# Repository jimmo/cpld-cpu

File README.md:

## CPLD CPU

This is a project to create a demonstration CPU that is simple enough to be able to watch its execution but also able to do something almost useful.

It was inspired by the following five projects:
 - [Fourbit, by Jaromir Sukuba](http://jaromir.xf.cz/fourbit/fourbit.html). This is a 4-bit CPU made entirely from 74xx series logic.
 - [Tiny CPU in a CPLD, by Big Mess o' Wires](https://www.bigmessowires.com/cpu-in-a-cpld/). This implements a whole CPU inside a single Altera CPLD.
 - [MCPU, by Tim Böscke](https://github.com/cpldcpu/MCPU) (and [writeup, by Jean-Claude Wippler](https://jeelabs.org/2017/11/tfoc---a-minimal-computer/)). Similar to above, but using the exact CPLD that I was intending to use, and with a really well-documented and practical ISA.
 - [The Megaprocessor, by James Newman](http://megaprocessor.com/). "The Megaprocessor is a micro-processor built large. Very large." Each gate is made from through-hole transistors with LEDs on all inputs and outputs.
 - [monster6502, by TubeTime & Evil Mad Scientist Laboratories](https://monster6502.com/). A working replica of the 6502 using discrete SMT transistors, complete with loads of LEDs.

In particular the CPU design (ISA and architecture) is inspired by Fourbit, Tiny CPU, and especially MPU, while the exploded design and "LEDs everywhere" is inspired by the Megaprocessor and monster6502. While nowhere near as capable as monster6502 or the Megaprocessor, it is definitely much more budget-friendly! And it can still [compute prime numbers](pysim/cpu_ax_13/tests/primes.s) ([video](https://www.youtube.com/watch?v=ZP9e-FCwwOs)) and [drive APA102 LED strips](pysim/cpu_ax_13/tests/apa102c.s).

Also, while not a direct inspiration to this project, it's absolutely worth linking to [Breadboard 8-bit computer, by Ben Eater](https://eater.net/8bit) which is a wonderful series about a similar project.

## History

This idea started when I was teaching an introduction to "how CPUs work", and wanted something tangible to show my students. The goal is to show how simple logic circuits (i.e. starting with AND and OR gates, flip flops, and a clock) can work together to do computation. No magic required.

Initially I planned to exactly replicate the Fourbit (possibly upgraded to 8-bit), but had trouble sourcing the 74181 ALU. I found a [XC9572XL CPLD development board](http://dangerousprototypes.com/blog/2011/03/29/new-prototype-xc9572xl-cpld-development-board/) in my board collection and considered replicating the 74181 on that. CPLDs are really useful for a project like this because they do not require external flash for configuration. You can use them almost as a complete drop-in replacement. However, at this point if you're not constraining yourself to using exactly 74xx series parts, then there are several simplifications you can make in the Fourbit design.

So I set about designing a CPU where each functional component is its own CPLD. In some ways this is similar to designing a soft-CPU for an FPGA, but with the additional constraint that signals between components actually need to go via physical pins. For an 8-bit CPU, this uses up a lot of pins very quickly.

For a fun side-quest, I wrote a [logic simulator](pysim) that allows a logic circuit to be defined in Python, and simulated, much the same way that [Verilator](https://www.veripool.org/verilator/) can simulate an HDL file. This allowed me to test and iterate on some different designs, including an [exact clone of the MCPU design](pysim/cpu_a_6). Additionally the simulator allows me to stay closer to my original goal of being able to describe every logic gate, although some shortcuts were taken.

The [final design](pysim/cpu_ax_13) expands on the MCPU design, including 13-bit addressing, an index register, two-byte instruction encoding, a primitive MMU allowing addressing up to 1MiB of physical RAM, and memory-mapped IO. The memory is von Neumann, allowing for RAM and ROM to share the same bus. The simulator allowed some [programs to be written](pysim/cpu_ax_13/tests) and tested, including an assembler supporting some macro commands.

Once that was working, I translated each Python component into VHDL, and tested it on the CPLD breakout board. For example, here's the decoder ([Python](pysim/cpu_ax_13/cpu.py#L51) and [VHDL](gateware/decoder/decoder.vhd)). The most difficult part of this process, and possibly the whole project, was [uploading the gateware to the CPLD](https://blog.jimmo.id.au/2018/11/26/programming-a-xc9500xl-cpld-with-a-raspberry-pi.html). In order to keep the design simple, the clock is generated by a ring oscillator in the clock CPLD, which is a terrible idea in general but works well here.

Finally, I designed [a schematic](hardware/schematic.pdf) and [PCB layout](hardware), which mostly involved laying out 131 LEDs (and their current limiting resistors). Rather than putting both RAM and ROM into the design, it just has a single RAM chip. This means that it has no persistent program storage, and the program needs to be loaded by an external programmer (implemented using some spare pins on the memory controller).

It's a four-layer PCB and can be assembled by hand with an iron or hot air. The CPLDs are TQFP and the LEDs and resistors are all 0805.

Other than occasionally being used for teaching, I mostly keep it mounted on the wall with the clock speed set to \~5Hz, forever [computing prime numbers](pysim/cpu_ax_13/tests/primes.s). It's quite mesmerizing to [watch](https://www.youtube.com/watch?v=ZP9e-FCwwOs)!

## Features

 - All internal state visible via 131 LEDs. This includes:
   - A, X, PC, Instr, and Addr registers (including carry & zero flags).
   - Data bus (and output/input state of each connected component)
   - Memory address
   - Clock
   - Decoder state
   - GPIO
 - 8-bit accumulator
 - 8-bit index register
 - 16-bit program counter
 - 8 instructions (nor a, add a, sta, jcc, nor x, add x, stx, jnz)
 - Variable-speed clock (Hz to >100kHz), including single-instruction and single-cycle step.
 - Expansion header (allowing for memory-mapped peripherals)
 - 8-bit memory-mapped GPIO port (input and output, with jumpered LEDs on each)
 - Serial programming header

## Instruction set

The instruction set is heavily inspired by MCPU. See their [project description](https://github.com/cpldcpu/MCPU/blob/master/mcpu.pdf?raw=true) and [blog post](https://jeelabs.org/2017/11/tfoc---a-minimal-computer/) for more information. The main extension is the addition of the index register (X) as well as a jump-non-zero.

### Hardware instructions

#### nor [mem]
`A = A nor [mem + X]`

#### add
`A = A + [mem + X]`

#### sta
`[mem + X] = A`

#### jcc
Jump if carry not set.

#### norx
`X = X nor [X]`

#### addx
`X = X + [mem]`

#### stx
`[mem] = X`

#### jnz
Jump if zero flag not set.

#### Pseudo instructions

These are supported by the assembler and generate a sequence of real instructions.

#### clr
`A = 0`

#### lda
`A = [mem]`

#### not
`A = ~A`

#### sub
`A = A - [mem + X]`

#### clrx
`X = 0`

#### ldx
`X = [mem]`

#### notx
`X = ~X`

#### subx
`X = X - [mem]`

#### jmp
Unconditional jump

#### jcs
Jump if carry flag set

#### jz
Jump if zero flag set

#### shl
`A = A << 1`

#### inc
`A = A + 1`

#### dec
`A = A - 1`

#### and
`A = A & [mem + X]`

#### or
`A = A | [mem + X]`

#### nand
`A = ~(A & [mem + X])`

#### xnor
`A = ~(A ^ [mem + X])`

#### xor
`A = A ^ [mem + X]`

#### ldpg
Sets the current memory page

#### hlt
Infinite loop

#### out
(Simulator only) prints A to stdout

## Programming

There's a [MicroPython script](programmer) that can load a assembled binary via the serial programming interface (header is next to the memory controller).

## TODO

 - Much more documentation and assembly guide (I'd love to do a video series one day)
 - Better demos
 - A higher-level compiler, making better use of the MMU
 - Design a peripheral to use the expansion connector
 - Use an external clock (and find out how fast this can go).

## Ideas for future revisions

 - Separate net for the LED ground (allowing it to be disconnected).
 - Fix the missing PC_LOW LED (bodged in on the current board)
 - More LEDs (e.g. ALU current operation)

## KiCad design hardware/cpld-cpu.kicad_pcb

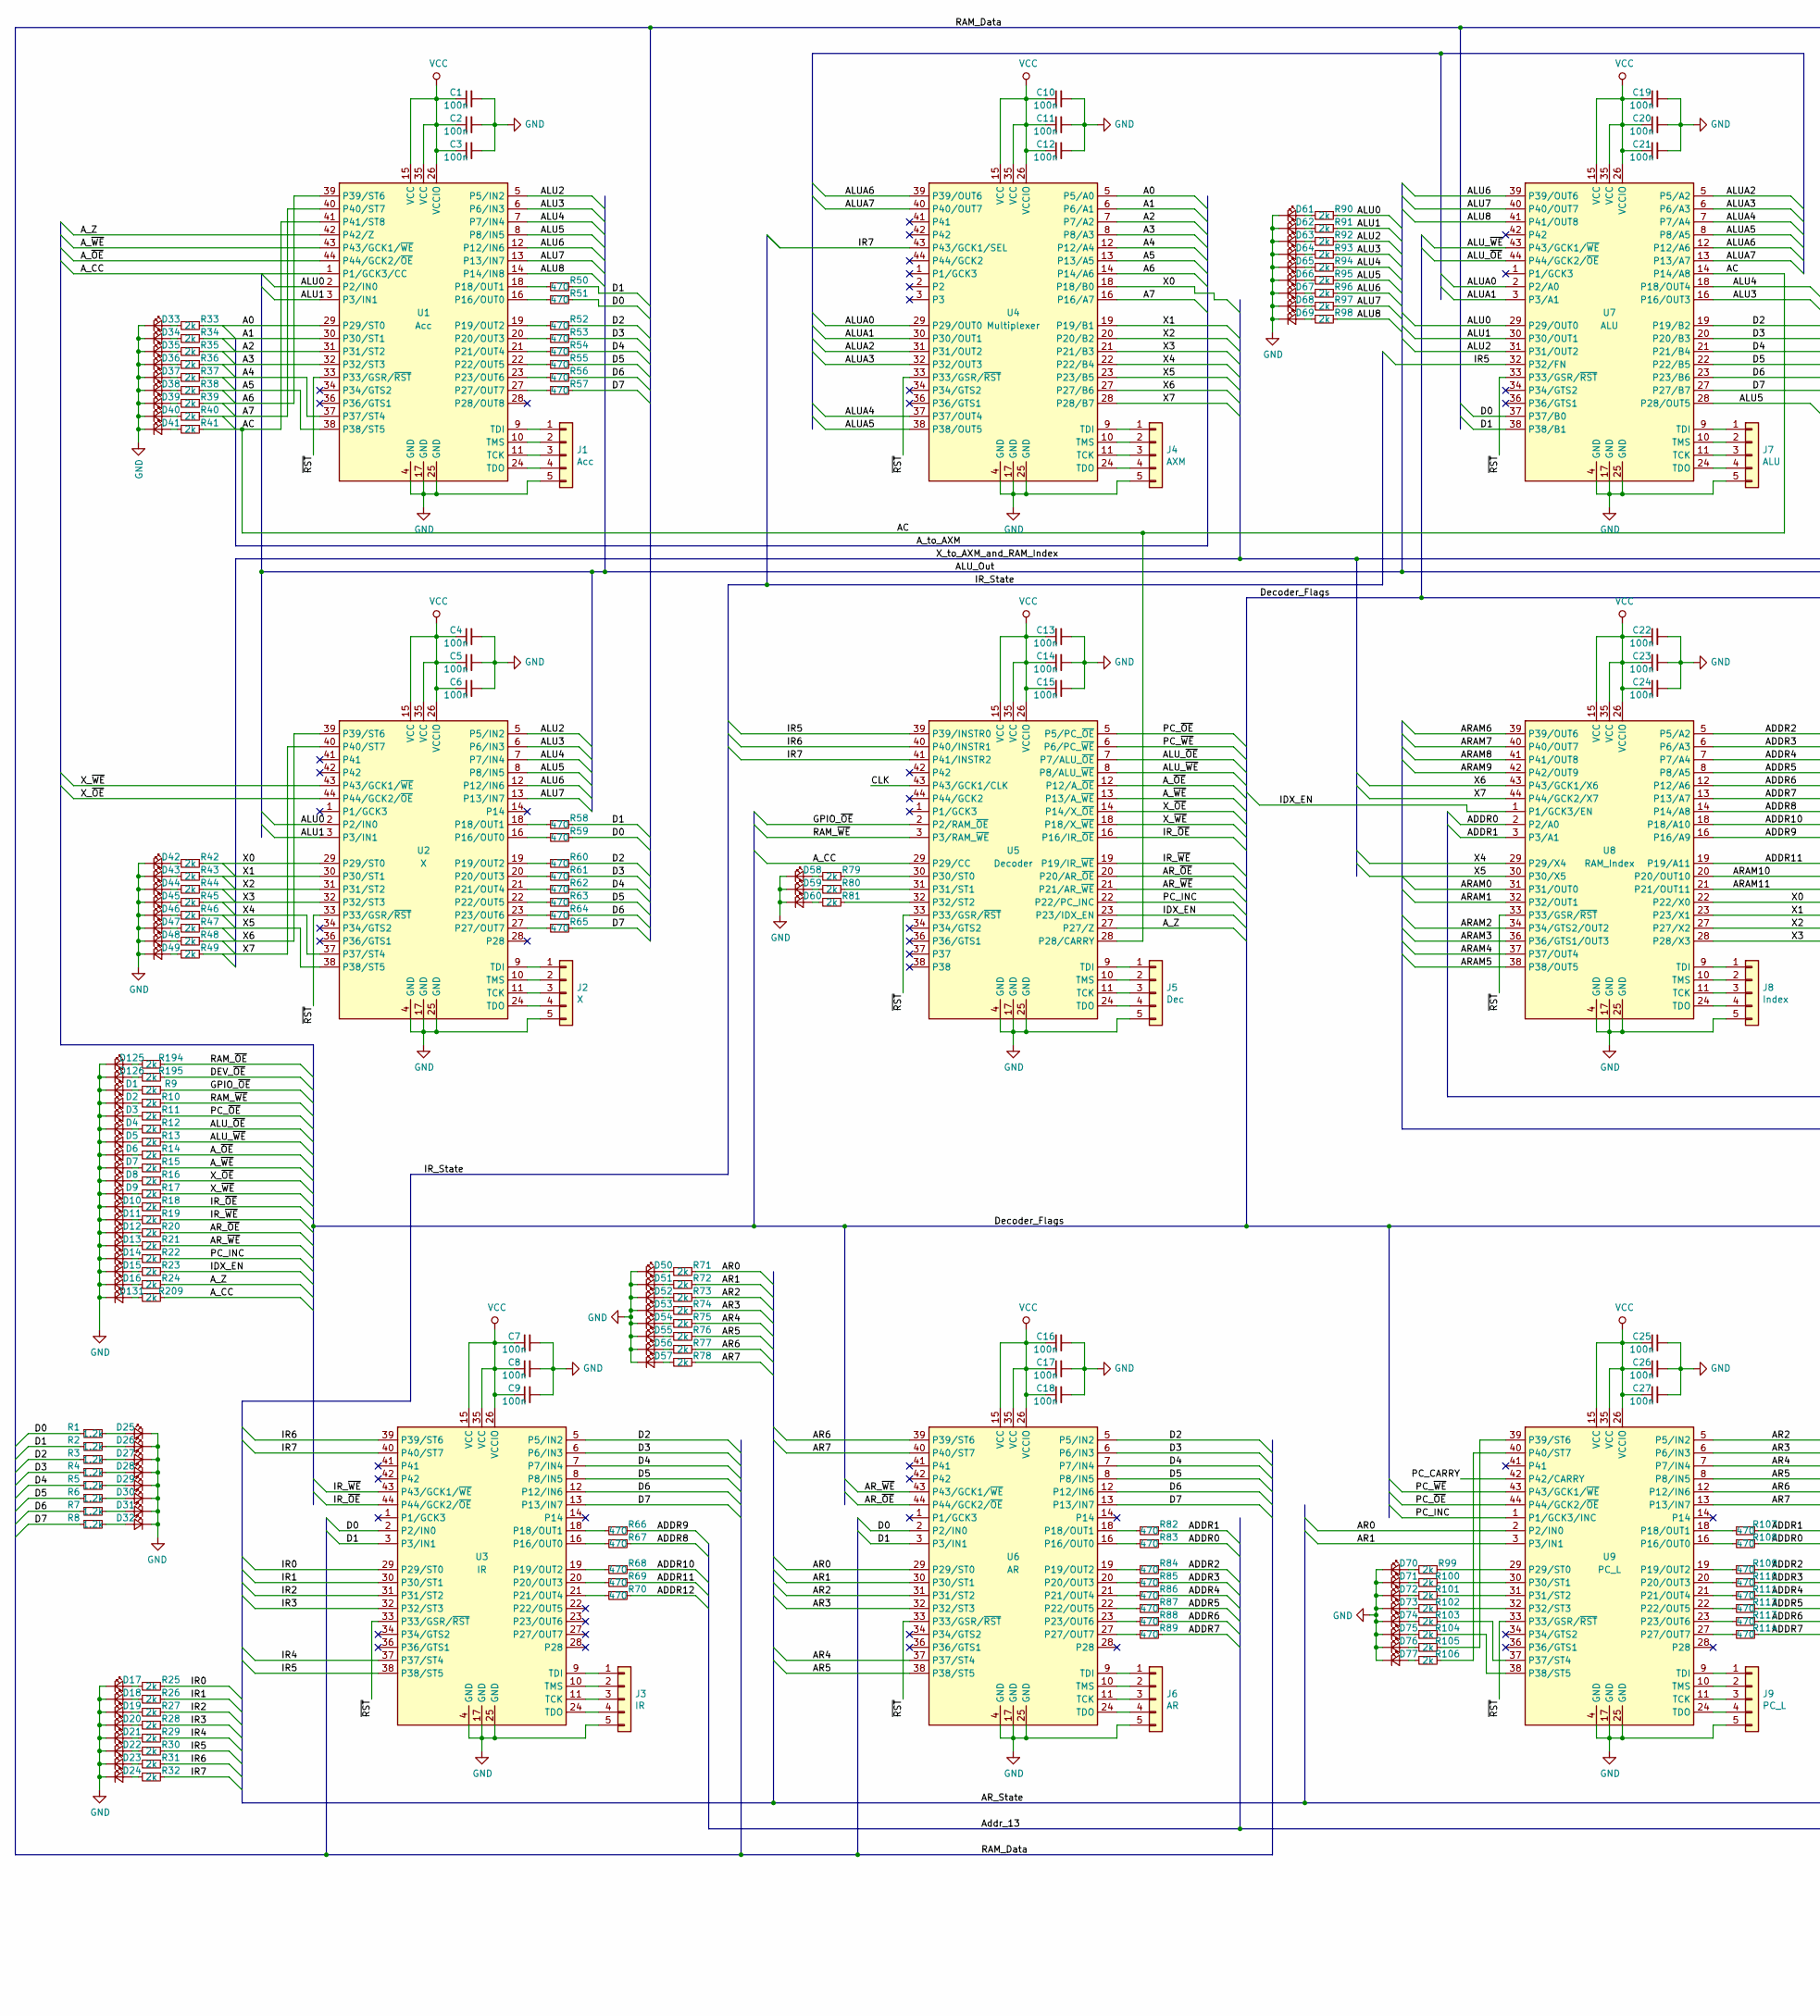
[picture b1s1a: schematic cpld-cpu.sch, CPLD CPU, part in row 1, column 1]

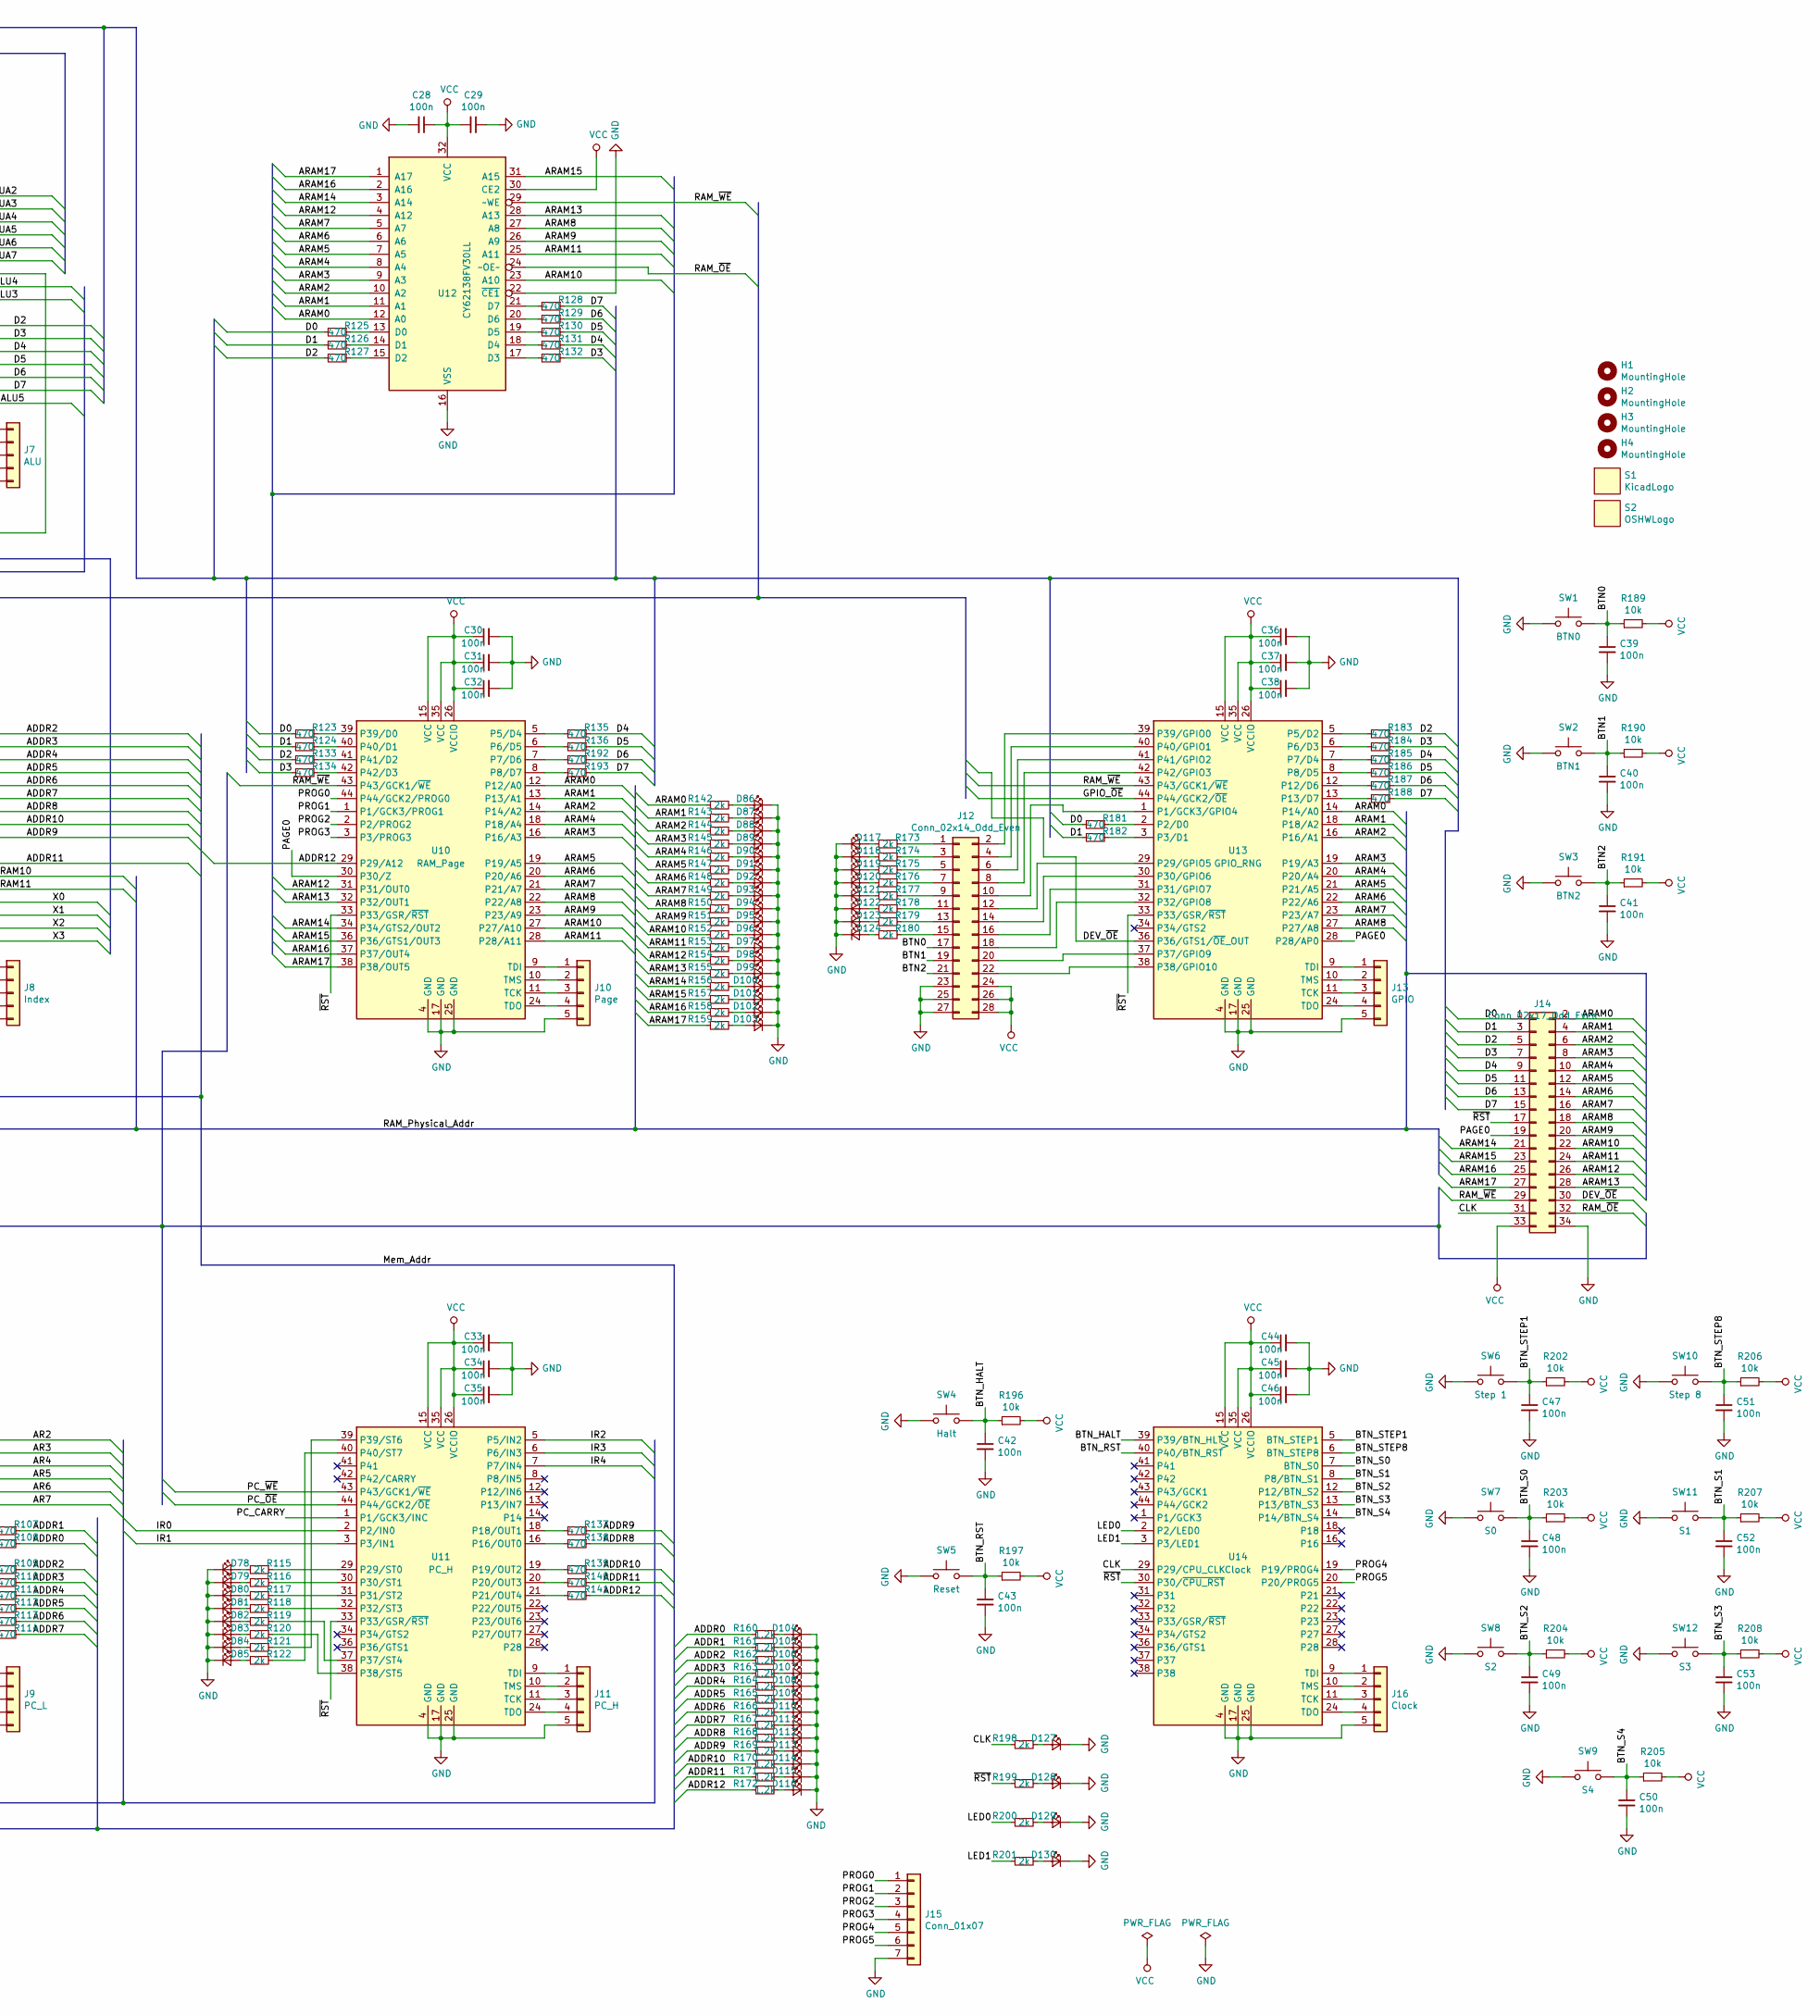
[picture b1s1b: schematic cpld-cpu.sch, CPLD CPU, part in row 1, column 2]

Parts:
C1, C2, C3, C4, C5, C6, C7, C8, C9, C10, C11, C12, C13, C14, C15, C16, C17, C18, C19, C20, C21, C22, C23, C24, C25, C26, C27, C28, C29, C30, C31, C32, C33, C34, C35, C36, C37, C38, C39, C40, C41, C42, C43, C44, C45, C46, C47, C48, C49, C50, C51, C52, C53: 100n; C_0805_HandSoldering
D1, D2, D3, D4, D5, D6, D7, D8, D9, D10, D11, D12, D13, D14, D15, D16, D17, D18, D19, D20, D21, D22, D23, D24, D25, D26, D27, D28, D29, D30, D31, D32, D33, D34, D35, D36, D37, D38, D39, D40, D41, D42, D43, D44, D45, D46, D47, D48, D49, D50, D51, D52, D53, D54, D55, D56, D57, D58, D59, D60, D61, D62, D63, D64, D65, D66, D67, D68, D69, D70, D71, D72, D73, D74, D75, D76, D77, D78, D79, D80, D81, D82, D83, D84, D85, D86, D87, D88, D89, D90, D91, D92, D93, D94, D95, D96, D97, D98, D99, D100, D101, D102, D103, D104, D105, D106, D107, D108, D109, D110, D111, D112, D113, D114, D115, D116, D117, D118, D119, D120, D121, D122, D123, D124, D125, D126, D127, D128, D129, D130, D131: LED_Small; LED_0805_HandSoldering
H1, H2, H3, H4: MountingHole; MountingHole_4.3mm_M4
J1: Acc; Pin_Header_Straight_1x05_Pitch2.54mm
J2: X; Pin_Header_Straight_1x05_Pitch2.54mm
J3: IR; Pin_Header_Straight_1x05_Pitch2.54mm
J4: AXM; Pin_Header_Straight_1x05_Pitch2.54mm
J5: Dec; Pin_Header_Straight_1x05_Pitch2.54mm
J6: AR; Pin_Header_Straight_1x05_Pitch2.54mm
J7: ALU; Pin_Header_Straight_1x05_Pitch2.54mm
J8: Index; Pin_Header_Straight_1x05_Pitch2.54mm
J9: PC_L; Pin_Header_Straight_1x05_Pitch2.54mm
J10: Page; Pin_Header_Straight_1x05_Pitch2.54mm
J11: PC_H; Pin_Header_Straight_1x05_Pitch2.54mm
J12: Conn_02x14_Odd_Even; Pin_Header_Straight_2x14_Pitch2.54mm
J13: GPIO; Pin_Header_Straight_1x05_Pitch2.54mm
J14: Conn_02x17_Odd_Even; Pin_Header_Straight_2x17_Pitch2.54mm
J15: Conn_01x07; Pin_Header_Straight_1x07_Pitch2.54mm
J16: Clock; Pin_Header_Straight_1x05_Pitch2.54mm
R1, R2, R3, R4, R5, R6, R7, R8, R160, R161, R162, R163, R164, R165, R166, R167, R168, R169, R170, R171, R172: 1.2k; R_0805_HandSoldering
R9, R10, R11, R12, R13, R14, R15, R16, R17, R18, R19, R20, R21, R22, R23, R24, R25, R26, R27, R28, R29, R30, R31, R32, R33, R34, R35, R36, R37, R38, R39, R40, R41, R42, R43, R44, R45, R46, R47, R48, R49, R71, R72, R73, R74, R75, R76, R77, R78, R79, R80, R81, R90, R91, R92, R93, R94, R95, R96, R97, R98, R99, R100, R101, R102, R103, R104, R105, R106, R115, R116, R117, R118, R119, R120, R121, R122, R142, R143, R144, R145, R146, R147, R148, R149, R150, R151, R152, R153, R154, R155, R156, R157, R158, R159, R173, R174, R175, R176, R177, R178, R179, R180, R194, R195, R198, R199, R200, R201, R209: 2k; R_0805_HandSoldering
R50, R51, R52, R53, R54, R55, R56, R57, R58, R59, R60, R61, R62, R63, R64, R65, R66, R67, R68, R69, R70, R82, R83, R84, R85, R86, R87, R88, R89, R107, R108, R109, R110, R111, R112, R113, R114, R123, R124, R125, R126, R127, R128, R129, R130, R131, R132, R133, R134, R135, R136, R137, R138, R139, R140, R141, R181, R182, R183, R184, R185, R186, R187, R188, R192, R193: 470; R_0805_HandSoldering
R189, R190, R191, R196, R197, R202, R203, R204, R205, R206, R207, R208: 10k; R_0805_HandSoldering
S1: KicadLogo; Symbol_KiCAD-Logo_CopperAndSilkScreenTop
S2: OSHWLogo; OSHW-Logo2_14.6x12mm_Copper_Top
SW1: BTN0; SW_SPST_B3S-1000
SW2: BTN1; SW_SPST_B3S-1000
SW3: BTN2; SW_SPST_B3S-1000
SW4: Halt; SW_SPST_B3S-1000
SW5: Reset; SW_SPST_B3S-1000
SW6: Step 1; SW_SPST_B3S-1000
SW7: S0; SW_SPST_B3S-1000
SW8: S2; SW_SPST_B3S-1000
SW9: S4; SW_SPST_B3S-1000
SW10: Step 8; SW_SPST_B3S-1000
SW11: S1; SW_SPST_B3S-1000
SW12: S3; SW_SPST_B3S-1000
U1: Acc; TQFP-44_10x10mm_Pitch0.8mm
U2: X; TQFP-44_10x10mm_Pitch0.8mm
U3: IR; TQFP-44_10x10mm_Pitch0.8mm
U4: Multiplexer; TQFP-44_10x10mm_Pitch0.8mm
U5: Decoder; TQFP-44_10x10mm_Pitch0.8mm
U6: AR; TQFP-44_10x10mm_Pitch0.8mm
U7: ALU; TQFP-44_10x10mm_Pitch0.8mm
U8: RAM_Index; TQFP-44_10x10mm_Pitch0.8mm
U9: PC_L; TQFP-44_10x10mm_Pitch0.8mm
U10: RAM_Page; TQFP-44_10x10mm_Pitch0.8mm
U11: PC_H; TQFP-44_10x10mm_Pitch0.8mm
U12: CY62138FV30LL; TSOP-II-32_21.0x10.2mm_Pitch1.27mm
U13: GPIO_RNG; TQFP-44_10x10mm_Pitch0.8mm
U14: Clock; TQFP-44_10x10mm_Pitch0.8mm

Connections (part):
/A0: R33.1, U1.29 (P29/ST0), U4.5 (P5/A0)
/A1: R34.1, U1.30 (P30/ST1), U4.6 (P6/A1)
/A2: R35.1, U1.31 (P31/ST2), U4.7 (P7/A2)
/A3: R36.1, U1.32 (P32/ST3), U4.8 (P8/A3)
/A4: R37.1, U1.37 (P37/ST4), U4.12 (P12/A4)
/A5: R38.1, U1.38 (P38/ST5), U4.13 (P13/A5)
/A6: R39.1, U1.39 (P39/ST6), U4.14 (P14/A6)
/A7: R40.1, U1.40 (P40/ST7), U4.16 (P16/A7)
/AC: R41.1, U1.41 (P41/ST8), U5.28 (P28/CARRY), U7.14 (P14/A8)
/ADDR0: R83.1, R108.1, R160.1, U8.2 (P2/A0)
/ADDR1: R82.1, R107.1, R161.1, U8.3 (P3/A1)
/ADDR2: R84.1, R109.1, R162.1, U8.5 (P5/A2)
/ADDR3: R85.1, R110.1, R163.1, U8.6 (P6/A3)
/ADDR4: R86.1, R111.1, R164.1, U8.7 (P7/A4)
/ADDR5: R87.1, R112.1, R165.1, U8.8 (P8/A5)
/ADDR6: R88.1, R113.1, R166.1, U8.12 (P12/A6)
/ADDR7: R89.1, R114.1, R167.1, U8.13 (P13/A7)
/ADDR8: R67.1, R138.1, R168.1, U8.14 (P14/A8)
/ADDR9: R66.1, R137.1, R169.1, U8.16 (P16/A9)
/ADDR10: R68.1, R139.1, R170.1, U8.18 (P18/A10)
/ADDR11: R69.1, R140.1, R171.1, U8.19 (P19/A11)
/ADDR12: R70.1, R141.1, R172.1, U10.29 (P29/A12)
/ALU0: R90.1, U1.2 (P2/IN0), U2.2 (P2/IN0), U7.29 (P29/OUT0)
/ALU1: R91.1, U1.3 (P3/IN1), U2.3 (P3/IN1), U7.30 (P30/OUT1)
/ALU2: R92.1, U1.5 (P5/IN2), U2.5 (P5/IN2), U7.31 (P31/OUT2)
/ALU3: R93.1, U1.6 (P6/IN3), U2.6 (P6/IN3), U7.16 (P16/OUT3)
/ALU4: R94.1, U1.7 (P7/IN4), U2.7 (P7/IN4), U7.18 (P18/OUT4)
/ALU5: R95.1, U1.8 (P8/IN5), U2.8 (P8/IN5), U7.28 (P28/OUT5)
/ALU6: R96.1, U1.12 (P12/IN6), U2.12 (P12/IN6), U7.39 (P39/OUT6)
/ALU7: R97.1, U1.13 (P13/IN7), U2.13 (P13/IN7), U7.40 (P40/OUT7)
/ALU8: R98.1, U1.14 (P14/IN8), U7.41 (P41/OUT8)
/ALUA0: U4.29 (P29/OUT0), U7.2 (P2/A0)
/ALUA1: U4.30 (P30/OUT1), U7.3 (P3/A1)
/ALUA2: U4.31 (P31/OUT2), U7.5 (P5/A2)
/ALUA3: U4.32 (P32/OUT3), U7.6 (P6/A3)
/ALUA4: U4.37 (P37/OUT4), U7.7 (P7/A4)
/ALUA5: U4.38 (P38/OUT5), U7.8 (P8/A5)
/ALUA6: U4.39 (P39/OUT6), U7.12 (P12/A6)
/ALUA7: U4.40 (P40/OUT7), U7.13 (P13/A7)
/ALU_~OE~: R12.1, U5.7 (P7/ALU_~OE~), U7.44 (P44/GCK2/~OE~)
/ALU_~WE~: R13.1, U5.8 (P8/ALU_~WE~), U7.43 (P43/GCK1/~WE~)
/AR0: R71.1, U6.29 (P29/ST0), U9.2 (P2/IN0)
/AR1: R72.1, U6.30 (P30/ST1), U9.3 (P3/IN1)
/AR2: R73.1, U6.31 (P31/ST2), U9.5 (P5/IN2)
/AR3: R74.1, U6.32 (P32/ST3), U9.6 (P6/IN3)
/AR4: R75.1, U6.37 (P37/ST4), U9.7 (P7/IN4)
/AR5: R76.1, U6.38 (P38/ST5), U9.8 (P8/IN5)
/AR6: R77.1, U6.39 (P39/ST6), U9.12 (P12/IN6)
/AR7: R78.1, U6.40 (P40/ST7), U9.13 (P13/IN7)
/ARAM0: J14.2, R142.1, U8.31 (P31/OUT0), U10.12 (P12/A0), U12.12 (A0), U13.14 (P14/A0)
/ARAM1: J14.4, R143.1, U8.32 (P32/OUT1), U10.13 (P13/A1), U12.11 (A1), U13.18 (P18/A2)
/ARAM2: J14.6, R144.1, U8.34 (P34/GTS2/OUT2), U10.14 (P14/A2), U12.10 (A2), U13.16 (P16/A1)
/ARAM3: J14.8, R145.1, U8.36 (P36/GTS1/OUT3), U10.16 (P16/A3), U12.9 (A3), U13.19 (P19/A3)
/ARAM4: J14.10, R146.1, U8.37 (P37/OUT4), U10.18 (P18/A4), U12.8 (A4), U13.20 (P20/A4)
/ARAM5: J14.12, R147.1, U8.38 (P38/OUT5), U10.19 (P19/A5), U12.7 (A5), U13.21 (P21/A5)
/ARAM6: J14.14, R148.1, U8.39 (P39/OUT6), U10.20 (P20/A6), U12.6 (A6), U13.22 (P22/A6)
/ARAM7: J14.16, R149.1, U8.40 (P40/OUT7), U10.21 (P21/A7), U12.5 (A7), U13.23 (P23/A7)
/ARAM8: J14.18, R150.1, U8.41 (P41/OUT8), U10.22 (P22/A8), U12.27 (A8), U13.27 (P27/A8)
/ARAM9: J14.20, R151.1, U8.42 (P42/OUT9), U10.23 (P23/A9), U12.26 (A9)
/ARAM10: J14.22, R152.1, U8.20 (P20/OUT10), U10.27 (P27/A10), U12.23 (A10)
/ARAM11: J14.24, R153.1, U8.21 (P21/OUT11), U10.28 (P28/A11), U12.25 (A11)
/ARAM12: J14.26, R154.1, U10.31 (P31/OUT0), U12.4 (A12)
/ARAM13: J14.28, R155.1, U10.32 (P32/OUT1), U12.28 (A13)
/ARAM14: J14.21, R156.1, U10.34 (P34/GTS2/OUT2), U12.3 (A14)
/ARAM15: J14.23, R157.1, U10.36 (P36/GTS1/OUT3), U12.31 (A15)
/ARAM16: J14.25, R158.1, U10.37 (P37/OUT4), U12.2 (A16)
/ARAM17: J14.27, R159.1, U10.38 (P38/OUT5), U12.1 (A17)
/AR_~OE~: R20.1, U5.20 (P20/AR_~OE~), U6.44 (P44/GCK2/~OE~)
/AR_~WE~: R21.1, U5.21 (P21/AR_~WE~), U6.43 (P43/GCK1/~WE~)
/A_CC: R209.1, U1.1 (P1/GCK3/CC), U5.29 (P29/CC)
/A_Z: R24.1, U1.42 (P42/Z), U5.27 (P27/Z)
/A_~OE~: R14.1, U1.44 (P44/GCK2/~OE~), U5.12 (P12/A_~OE~)
/A_~WE~: R15.1, U1.43 (P43/GCK1/~WE~), U5.13 (P13/A_~WE~)
/BTN0: C39.1, J12.17, R189.1, SW1.2
/BTN1: C40.1, J12.19, R190.1, SW2.2
/BTN2: C41.1, J12.21, R191.1, SW3.2
/BTN_HALT: C42.1, R196.1, SW4.2, U14.39 (P39/BTN_HLT)
/BTN_RST: C43.1, R197.1, SW5.2, U14.40 (P40/BTN_RST)
/BTN_S0: C48.1, R203.1, SW7.2, U14.7 (BTN_S0)
/BTN_S1: C52.1, R207.1, SW11.2, U14.8 (P8/BTN_S1)
/BTN_S2: C49.1, R204.1, SW8.2, U14.12 (P12/BTN_S2)
/BTN_S3: C53.1, R208.1, SW12.2, U14.13 (P13/BTN_S3)
/BTN_S4: C50.1, R205.1, SW9.2, U14.14 (P14/BTN_S4)
/BTN_STEP1: C47.1, R202.1, SW6.2, U14.5 (BTN_STEP1)
/BTN_STEP8: C51.1, R206.1, SW10.2, U14.6 (BTN_STEP8)
/CLK: J14.31, R198.1, U5.43 (P43/GCK1/CLK), U14.29 (P29/CPU_CLK)
/D0: J14.1, R1.1, R51.1, R59.1, R123.2, R125.2, R181.2, U3.2 (P2/IN0), U6.2 (P2/IN0), U7.37 (P37/B0)
/D1: J14.3, R2.1, R50.1, R58.1, R124.2, R126.2, R182.2, U3.3 (P3/IN1), U6.3 (P3/IN1), U7.38 (P38/B1)
/D2: J14.5, R3.1, R52.1, R60.1, R127.2, R133.2, R183.1, U3.5 (P5/IN2), U6.5 (P5/IN2), U7.19 (P19/B2)
/D3: J14.7, R4.1, R53.1, R61.1, R132.1, R134.2, R184.1, U3.6 (P6/IN3), U6.6 (P6/IN3), U7.20 (P20/B3)
/D4: J14.9, R5.1, R54.1, R62.1, R131.1, R135.1, R185.1, U3.7 (P7/IN4), U6.7 (P7/IN4), U7.21 (P21/B4)
/D5: J14.11, R6.1, R55.1, R63.1, R130.1, R136.1, R186.1, U3.8 (P8/IN5), U6.8 (P8/IN5), U7.22 (P22/B5)
/D6: J14.13, R7.1, R56.1, R64.1, R129.1, R187.1, R192.1, U3.12 (P12/IN6), U6.12 (P12/IN6), U7.23 (P23/B6)
/D7: J14.15, R8.1, R57.1, R65.1, R128.1, R188.1, R193.1, U3.13 (P13/IN7), U6.13 (P13/IN7), U7.27 (P27/B7)
/DEV_~OE~: J14.30, R195.1, U13.36 (P36/GTS1/~OE~_OUT)
/GPIO_~OE~: R9.1, U5.2 (P2/RAM_~OE~), U13.44 (P44/GCK2/~OE~)
/IDX_EN: R23.1, U5.23 (P23/IDX_EN), U8.1 (P1/GCK3/EN)
/IR0: R25.1, U3.29 (P29/ST0), U11.2 (P2/IN0)
/IR1: R26.1, U3.30 (P30/ST1), U11.3 (P3/IN1)
/IR2: R27.1, U3.31 (P31/ST2), U11.5 (P5/IN2)
/IR3: R28.1, U3.32 (P32/ST3), U11.6 (P6/IN3)
/IR4: R29.1, U3.37 (P37/ST4), U11.7 (P7/IN4)
/IR5: R30.1, U3.38 (P38/ST5), U5.39 (P39/INSTR0), U7.32 (P32/FN)
/IR6: R31.1, U3.39 (P39/ST6), U5.40 (P40/INSTR1)
/IR7: R32.1, U3.40 (P40/ST7), U4.43 (P43/GCK1/SEL), U5.41 (P41/INSTR2)
/IR_~OE~: R18.1, U3.44 (P44/GCK2/~OE~), U5.16 (P16/IR_~OE~)
/IR_~WE~: R19.1, U3.43 (P43/GCK1/~WE~), U5.19 (P19/IR_~WE~)
/LED0: R200.1, U14.2 (P2/LED0)
/LED1: R201.1, U14.3 (P3/LED1)
/PAGE0: J14.19, U10.30 (P30/Z), U13.28 (P28/AP0)
/PC_CARRY: U9.42 (P42/CARRY), U11.1 (P1/GCK3/INC)
/PC_INC: R22.1, U5.22 (P22/PC_INC), U9.1 (P1/GCK3/INC)
/PC_~OE~: R11.1, U5.5 (P5/PC_~OE~), U9.44 (P44/GCK2/~OE~), U11.44 (P44/GCK2/~OE~)
/PC_~WE~: U5.6 (P6/PC_~WE~), U9.43 (P43/GCK1/~WE~), U11.43 (P43/GCK1/~WE~)
/PROG0: J15.1, U10.44 (P44/GCK2/PROG0)
/PROG1: J15.2, U10.1 (P1/GCK3/PROG1)
/PROG2: J15.3, U10.2 (P2/PROG2)
/PROG3: J15.4, U10.3 (P3/PROG3)
/PROG4: J15.5, U14.19 (P19/PROG4)
/PROG5: J15.6, U14.20 (P20/PROG5)
/RAM_~OE~: J14.32, R194.1, U12.24 (~~OE~~)
/RAM_~WE~: J14.29, R10.1, U5.3 (P3/RAM_~WE~), U10.43 (P43/GCK1/~WE~), U12.29 (~~WE~), U13.43 (P43/GCK1/~WE~)
/X0: R42.1, U2.29 (P29/ST0), U4.18 (P18/B0), U8.22 (P22/X0)
/X1: R43.1, U2.30 (P30/ST1), U4.19 (P19/B1), U8.23 (P23/X1)
/X2: R44.1, U2.31 (P31/ST2), U4.20 (P20/B2), U8.27 (P27/X2)
/X3: R45.1, U2.32 (P32/ST3), U4.21 (P21/B3), U8.28 (P28/X3)
/X4: R46.1, U2.37 (P37/ST4), U4.22 (P22/B4), U8.29 (P29/X4)
/X5: R47.1, U2.38 (P38/ST5), U4.23 (P23/B5), U8.30 (P30/X5)
/X6: R48.1, U2.39 (P39/ST6), U4.27 (P27/B6), U8.43 (P43/GCK1/X6)
/X7: R49.1, U2.40 (P40/ST7), U4.28 (P28/B7), U8.44 (P44/GCK2/X7)
/X_~OE~: R16.1, U2.44 (P44/GCK2/~OE~), U5.14 (P14/X_~OE~)
/X_~WE~: R17.1, U2.43 (P43/GCK1/~WE~), U5.18 (P18/X_~WE~)
/~RST~: J14.17, R199.1, U1.33 (P33/GSR/~RST), U2.33 (P33/GSR/~RST), U3.33 (P33/GSR/~RST), U4.33 (P33/GSR/~RST), U5.33 (P33/GSR/~RST), U6.33 (P33/GSR/~RST), U7.33 (P33/GSR/~RST), U8.33 (P33/GSR/~RST), U9.33 (P33/GSR/~RST), U10.33 (P33/GSR/~RST), U11.33 (P33/GSR/~RST), U13.33 (P33/GSR/~RST), U14.30 (P30/~CPU_RST~)
GND: C1.2, C2.2, C3.2, C4.2, C5.2, C6.2, C7.2, C8.2, C9.2, C10.2, C11.2, C12.2, C13.2, C14.2, C15.2, C16.2, C17.2, C18.2, C19.2, C20.2, C21.2, C22.2, C23.2, C24.2, C25.2, C26.2, C27.2, C28.2, C29.1, C30.2, C31.2, C32.2, C33.2, C34.2, C35.2, C36.2, C37.2, C38.2, C39.2, C40.2, C41.2, C42.2, C43.2, C44.2, C45.2, C46.2, C47.2, C48.2, C49.2, C50.2, C51.2, C52.2, C53.2, D1.1 (K), D2.1 (K), D3.1 (K), D4.1 (K), D5.1 (K), D6.1 (K), D7.1 (K), D8.1 (K), D9.1 (K), D10.1 (K), D11.1 (K), D12.1 (K), D13.1 (K), D14.1 (K), D15.1 (K), D16.1 (K), D17.1 (K), D18.1 (K), D19.1 (K), D20.1 (K), D21.1 (K), D22.1 (K), D23.1 (K), D24.1 (K), D25.1 (K), D26.1 (K), D27.1 (K), D28.1 (K)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
unnamed: D1.2 (A), R9.2
unnamed: D2.2 (A), R10.2
unnamed: D3.2 (A), R11.2
unnamed: D4.2 (A), R12.2
unnamed: D5.2 (A), R13.2
unnamed: D6.2 (A), R14.2
unnamed: D7.2 (A), R15.2
unnamed: D8.2 (A), R16.2
unnamed: D9.2 (A), R17.2
unnamed: D10.2 (A), R18.2
unnamed: D11.2 (A), R19.2
unnamed: D12.2 (A), R20.2
unnamed: D13.2 (A), R21.2
unnamed: D14.2 (A), R22.2
unnamed: D15.2 (A), R23.2
unnamed: D16.2 (A), R24.2
unnamed: D17.2 (A), R25.2
unnamed: D18.2 (A), R26.2
unnamed: D19.2 (A), R27.2
unnamed: D20.2 (A), R28.2
unnamed: D21.2 (A), R29.2
unnamed: D22.2 (A), R30.2
unnamed: D23.2 (A), R31.2
unnamed: D24.2 (A), R32.2
unnamed: D25.2 (A), R1.2
unnamed: D26.2 (A), R2.2
unnamed: D27.2 (A), R3.2
unnamed: D28.2 (A), R4.2
unnamed: D29.2 (A), R5.2
unnamed: D30.2 (A), R6.2
unnamed: D31.2 (A), R7.2
unnamed: D32.2 (A), R8.2
unnamed: D33.2 (A), R33.2
unnamed: D34.2 (A), R34.2
unnamed: D35.2 (A), R35.2
unnamed: D36.2 (A), R36.2
unnamed: D37.2 (A), R37.2
unnamed: D38.2 (A), R38.2
unnamed: D39.2 (A), R39.2
unnamed: D40.2 (A), R40.2
unnamed: D41.2 (A), R41.2
unnamed: D42.2 (A), R42.2
unnamed: D43.2 (A), R43.2
unnamed: D44.2 (A), R44.2
unnamed: D45.2 (A), R45.2
unnamed: D46.2 (A), R46.2
unnamed: D47.2 (A), R47.2
unnamed: D48.2 (A), R48.2
unnamed: D49.2 (A), R49.2
unnamed: D50.2 (A), R71.2
unnamed: D51.2 (A), R72.2
unnamed: D52.2 (A), R73.2
unnamed: D53.2 (A), R74.2
unnamed: D54.2 (A), R75.2
unnamed: D55.2 (A), R76.2
unnamed: D56.2 (A), R77.2
unnamed: D57.2 (A), R78.2
unnamed: D58.2 (A), R79.2
unnamed: D59.2 (A), R80.2
unnamed: D60.2 (A), R81.2
unnamed: D61.2 (A), R90.2
unnamed: D62.2 (A), R91.2
unnamed: D63.2 (A), R92.2
unnamed: D64.2 (A), R93.2
unnamed: D65.2 (A), R94.2
unnamed: D66.2 (A), R95.2
unnamed: D67.2 (A), R96.2
unnamed: D68.2 (A), R97.2
unnamed: D69.2 (A), R98.2
unnamed: D70.2 (A), R99.2
unnamed: D71.2 (A), R100.2
unnamed: D72.2 (A), R101.2
unnamed: D73.2 (A), R102.2
unnamed: D74.2 (A), R103.2
unnamed: D75.2 (A), R104.2
unnamed: D76.2 (A), R105.2
unnamed: D77.2 (A), R106.2
unnamed: D78.2 (A), R115.2
unnamed: D79.2 (A), R116.2
unnamed: D80.2 (A), R117.2
unnamed: D81.2 (A), R118.2
unnamed: D82.2 (A), R119.2
unnamed: D83.2 (A), R120.2
unnamed: D84.2 (A), R121.2
unnamed: D85.2 (A), R122.2
unnamed: D86.2 (A), R142.2
unnamed: D87.2 (A), R143.2
unnamed: D88.2 (A), R144.2
unnamed: D89.2 (A), R145.2
unnamed: D90.2 (A), R146.2
unnamed: D91.2 (A), R147.2
unnamed: D92.2 (A), R148.2
unnamed: D93.2 (A), R149.2
unnamed: D94.2 (A), R150.2
unnamed: D95.2 (A), R151.2
unnamed: D96.2 (A), R152.2
unnamed: D97.2 (A), R153.2
unnamed: D98.2 (A), R154.2
unnamed: D99.2 (A), R155.2
unnamed: D100.2 (A), R156.2
unnamed: D101.2 (A), R157.2
unnamed: D102.2 (A), R158.2
unnamed: D103.2 (A), R159.2
unnamed: D104.2 (A), R160.2
unnamed: D105.2 (A), R161.2
unnamed: D106.2 (A), R162.2
unnamed: D107.2 (A), R163.2
unnamed: D108.2 (A), R164.2
unnamed: D109.2 (A), R165.2
unnamed: D110.2 (A), R166.2
unnamed: D111.2 (A), R167.2
unnamed: D112.2 (A), R168.2
unnamed: D113.2 (A), R169.2
unnamed: D114.2 (A), R170.2
unnamed: D115.2 (A), R171.2
unnamed: D116.2 (A), R172.2
unnamed: D117.2 (A), R173.2
unnamed: D118.2 (A), R174.2
unnamed: D119.2 (A), R175.2
unnamed: D120.2 (A), R176.2
unnamed: D121.2 (A), R177.2
unnamed: D122.2 (A), R178.2
unnamed: D123.2 (A), R179.2
unnamed: D124.2 (A), R180.2
unnamed: D125.2 (A), R194.2
unnamed: D126.2 (A), R195.2
unnamed: D127.2 (A), R198.2
unnamed: D128.2 (A), R199.2
unnamed: D129.2 (A), R200.2
unnamed: D130.2 (A), R201.2
unnamed: D131.2 (A), R209.2
unnamed: J1.1, U1.9 (TDI)
unnamed: J1.2, U1.10 (TMS)
unnamed: J1.3, U1.11 (TCK)
unnamed: J1.4, U1.24 (TDO)
unnamed: J2.1, U2.9 (TDI)
unnamed: J2.2, U2.10 (TMS)
unnamed: J2.3, U2.11 (TCK)
unnamed: J2.4, U2.24 (TDO)
unnamed: J3.1, U3.9 (TDI)
unnamed: J3.2, U3.10 (TMS)
unnamed: J3.3, U3.11 (TCK)
unnamed: J3.4, U3.24 (TDO)
unnamed: J4.1, U4.9 (TDI)
unnamed: J4.2, U4.10 (TMS)
unnamed: J4.3, U4.11 (TCK)
unnamed: J4.4, U4.24 (TDO)
unnamed: J5.1, U5.9 (TDI)
unnamed: J5.2, U5.10 (TMS)
unnamed: J5.3, U5.11 (TCK)
unnamed: J5.4, U5.24 (TDO)
unnamed: J6.1, U6.9 (TDI)
unnamed: J6.2, U6.10 (TMS)
unnamed: J6.3, U6.11 (TCK)
unnamed: J6.4, U6.24 (TDO)
unnamed: J7.1, U7.9 (TDI)
unnamed: J7.2, U7.10 (TMS)
unnamed: J7.3, U7.11 (TCK)
unnamed: J7.4, U7.24 (TDO)
unnamed: J8.1, U8.9 (TDI)
unnamed: J8.2, U8.10 (TMS)
unnamed: J8.3, U8.11 (TCK)
unnamed: J8.4, U8.24 (TDO)
unnamed: J9.1, U9.9 (TDI)
unnamed: J9.2, U9.10 (TMS)
unnamed: J9.3, U9.11 (TCK)
unnamed: J9.4, U9.24 (TDO)
unnamed: J10.1, U10.9 (TDI)
unnamed: J10.2, U10.10 (TMS)
unnamed: J10.3, U10.11 (TCK)
unnamed: J10.4, U10.24 (TDO)
unnamed: J11.1, U11.9 (TDI)
unnamed: J11.2, U11.10 (TMS)
unnamed: J11.3, U11.11 (TCK)
unnamed: J11.4, U11.24 (TDO)
unnamed: J12.1, R173.1
unnamed: J12.2, U13.39 (P39/GPIO0)
unnamed: J12.3, R174.1
unnamed: J12.4, U13.40 (P40/GPIO1)
unnamed: J12.5, R175.1
unnamed: J12.6, U13.41 (P41/GPIO2)
unnamed: J12.7, R176.1
unnamed: J12.8, U13.42 (P42/GPIO3)
unnamed: J12.9, R177.1
unnamed: J12.10, U13.1 (P1/GCK3/GPIO4)
unnamed: J12.11, R178.1
unnamed: J12.12, U13.29 (P29/GPIO5)
unnamed: J12.13, R179.1
unnamed: J12.14, U13.30 (P30/GPIO6)
unnamed: J12.15, R180.1
unnamed: J12.16, U13.31 (P31/GPIO7)
unnamed: J12.18, U13.32 (P32/GPIO8)
unnamed: J12.20, U13.37 (P37/GPIO9)
unnamed: J12.22, U13.38 (P38/GPIO10)
unnamed: J13.1, U13.9 (TDI)
unnamed: J13.2, U13.10 (TMS)
unnamed: J13.3, U13.11 (TCK)
unnamed: J13.4, U13.24 (TDO)
unnamed: J16.1, U14.9 (TDI)
unnamed: J16.2, U14.10 (TMS)
unnamed: J16.3, U14.11 (TCK)
unnamed: J16.4, U14.24 (TDO)
unnamed: R50.2, U1.18 (P18/OUT1)
unnamed: R51.2, U1.16 (P16/OUT0)
unnamed: R52.2, U1.19 (P19/OUT2)
unnamed: R53.2, U1.20 (P20/OUT3)
unnamed: R54.2, U1.21 (P21/OUT4)
unnamed: R55.2, U1.22 (P22/OUT5)
unnamed: R56.2, U1.23 (P23/OUT6)
unnamed: R57.2, U1.27 (P27/OUT7)
unnamed: R58.2, U2.18 (P18/OUT1)
unnamed: R59.2, U2.16 (P16/OUT0)
unnamed: R60.2, U2.19 (P19/OUT2)
unnamed: R61.2, U2.20 (P20/OUT3)
unnamed: R62.2, U2.21 (P21/OUT4)
unnamed: R63.2, U2.22 (P22/OUT5)
unnamed: R64.2, U2.23 (P23/OUT6)
unnamed: R65.2, U2.27 (P27/OUT7)
unnamed: R66.2, U3.18 (P18/OUT1)
unnamed: R67.2, U3.16 (P16/OUT0)
unnamed: R68.2, U3.19 (P19/OUT2)
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
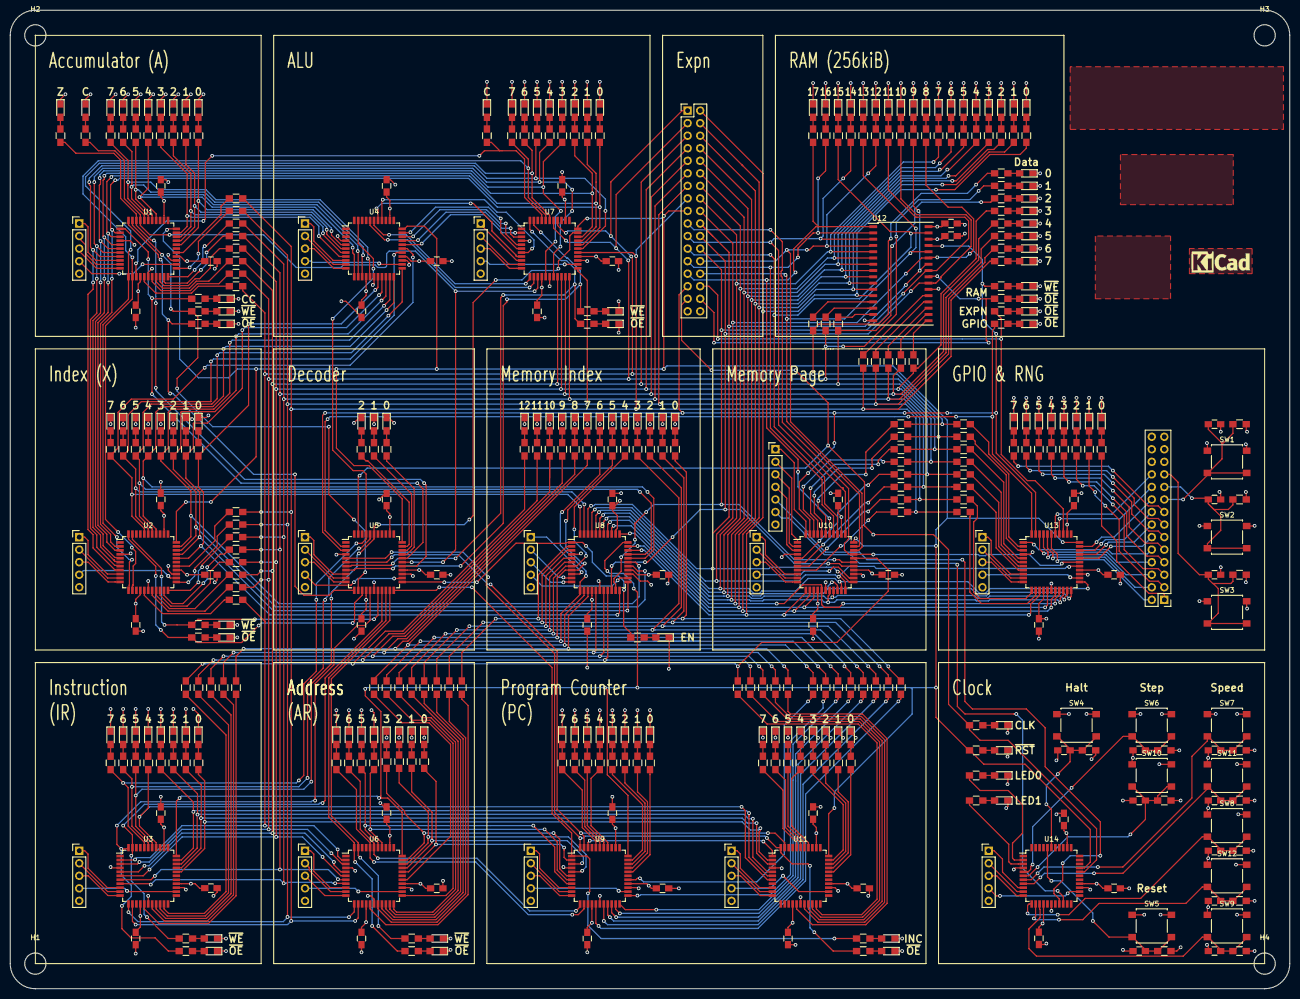
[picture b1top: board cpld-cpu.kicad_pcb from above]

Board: 4 copper layers, 259.1 x 198.1 mm, 441 parts (0 on the bottom side), 422 nets.

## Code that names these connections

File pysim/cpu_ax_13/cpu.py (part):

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        self.last_clk = None

    def reset(self):
        self.ram_oe <<= 0
        self.ram_we <<= 0
        self.ar_oe <<= 0
        self.ar_we <<= 0
        self.ir_oe <<= 0
        self.ir_we <<= 0
        self.pc_we <<= 0
        self.pc_oe <<= 0
        self.pc_inc <<= 0
        self.a_oe <<= 0
        self.a_we <<= 0
        self.a_cc <<= 0
        self.x_oe <<= 0
        self.x_we <<= 0
        self.alu_oe <<= 1
        self.alu_we <<= 0
        self.idx_en <<= 0

    def update(self, signal):
        if self.clk.value() != self.last_clk:
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
        self.ar_oe <<= self.state > 3
        self.ir_oe <<= self.state > 3
        self.pc_oe <<= self.state <= 3
        self.ir_we <<= self.state == 1
        self.pc_inc <<= self.state in (
            2,
            4,
        )
        self.ar_we <<= self.state == 3

        # alu
        self.alu_we <<= (
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            )
            and self.state == 6
        )
        self.x_we <<= self.instr.value() in (0b100, 0b101) and self.state == 6

        # sta/stx
        self.a_oe <<= self.instr.value() == 0b010 and self.state in (
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
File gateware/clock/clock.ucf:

net led0 loc=pin2;
net led1 loc=pin3;
net btn_halt loc=pin39;
net btn_rst loc=pin40;
net btn_step1 loc=pin5;
net btn_step8 loc=pin6;
net btn_s0 loc=pin7;
net btn_s1 loc=pin8;
net btn_s2 loc=pin12;
net btn_s3 loc=pin13;
net btn_s4 loc=pin14;
net prog4 loc=pin19;
net prog5 loc=pin20;
net cpu_clk loc=pin29;
net cpu_rst loc=pin30;
net nrst loc=pin33;
